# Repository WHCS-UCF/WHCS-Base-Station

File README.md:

# WHCS Base Station Design

The KiCad source files for WHCS' base station board.
The published rev 1.0 board is available on [OSHPark](https://oshpark.com/shared_projects/1ZnSgowG).

## Requirements
KiCad 2013-05-18 and some extra libraries

## Board Front

## Board Back

### Author
Grant Hernandez<br/>
*Computer Engineer*

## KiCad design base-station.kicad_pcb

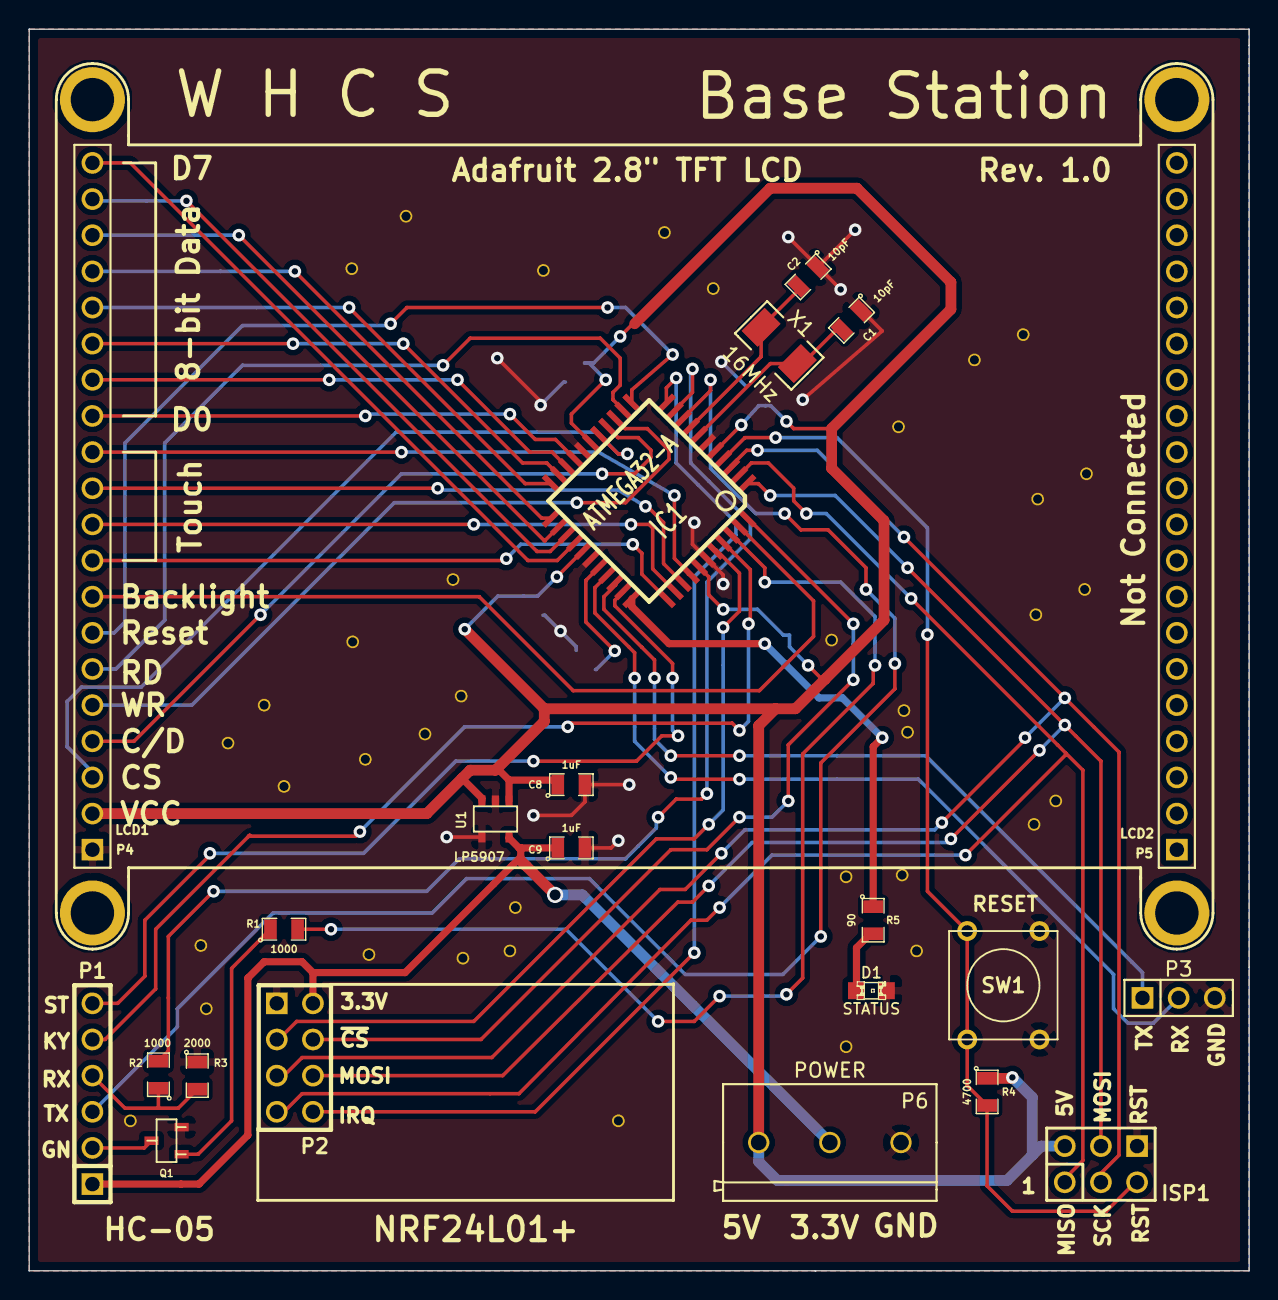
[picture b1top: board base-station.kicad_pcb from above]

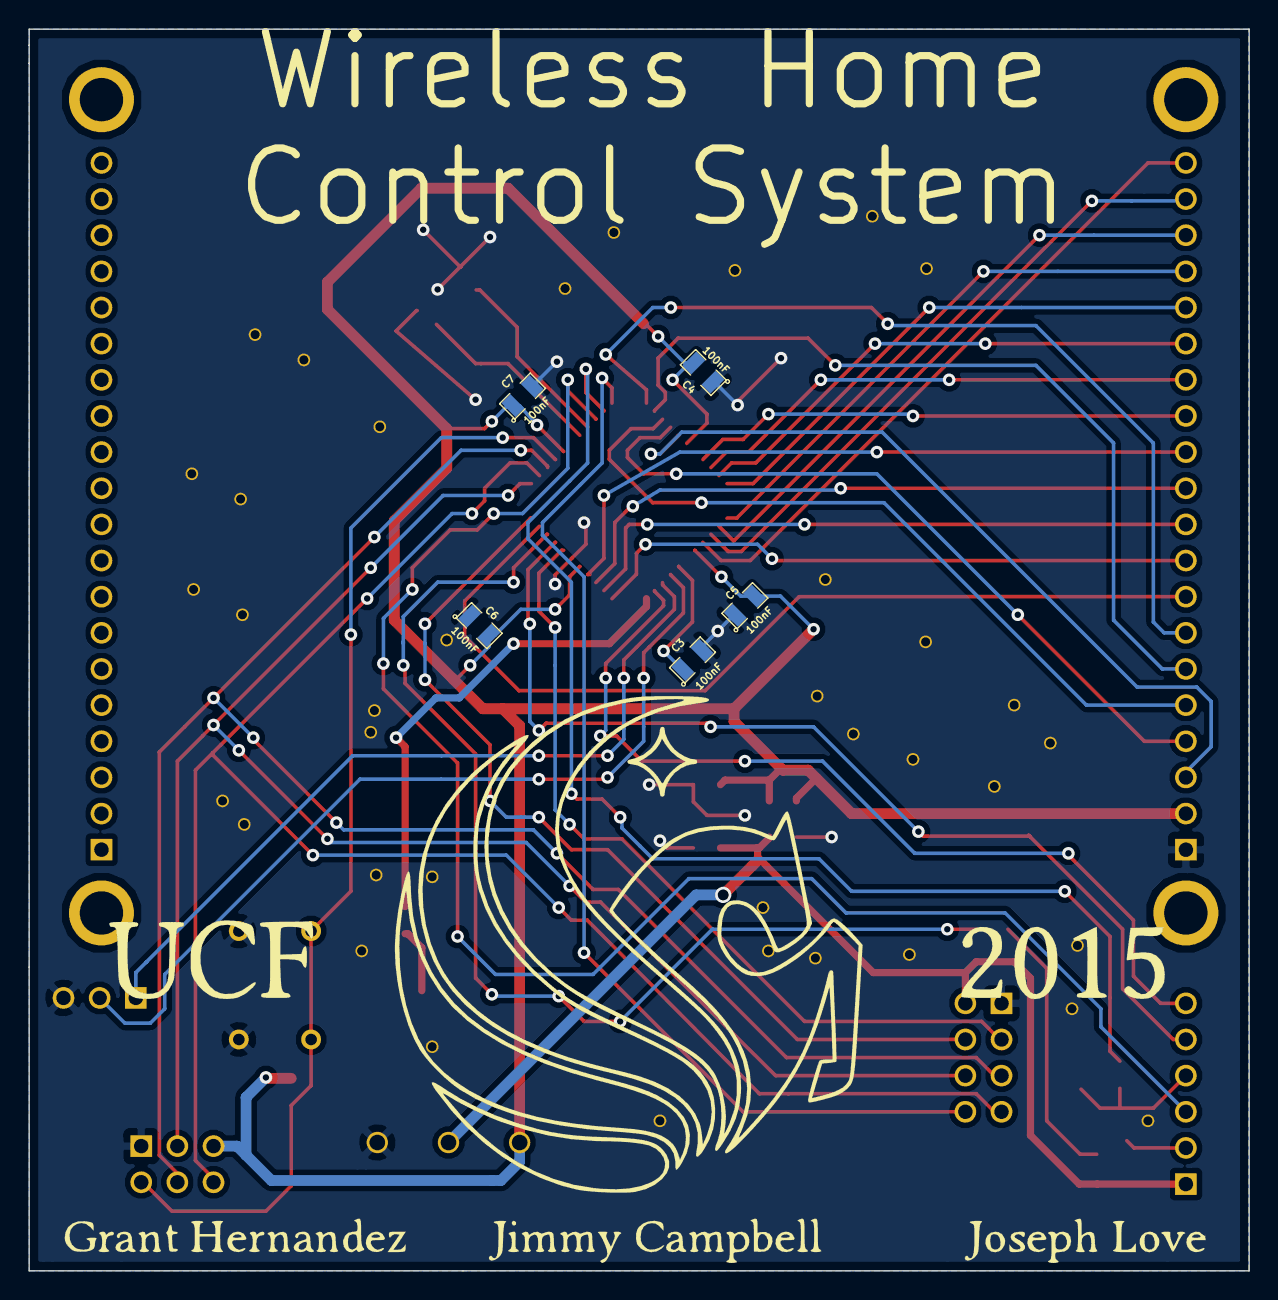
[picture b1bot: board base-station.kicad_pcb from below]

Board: 2 copper layers, 85.7 x 87.2 mm, 27 parts (5 on the bottom side), 43 nets.

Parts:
C1, C2: 10pF; SM0805
C3, C4, C5, C6, C7: 100nF; SM0805
C8, C9: 1uF; SM0805
D1: STATUS; LED-0805
IC1: ATMEGA32-A; TQFP44
ISP1: ISP; pin_array_3x2
P1: HC-05; PIN_ARRAY-6X1
P2: NRF24L01+; pin_array_4x2
P3: SERIAL; PIN_ARRAY_3X1
P4: LCD1; PIN_ARRAY_20X1
P5: LCD2; PIN_ARRAY_20X1
P6: POWER; terminal-282836-3
Q1: BTEN; sot23
R1, R2: 1000; SM0805
R3: 2000; SM0805
R4: 4700; SM0805
R5: 90; SM0805
SW1: RESET; SW_PUSH_SMALL
U1: LP5907; SOT23-5
X1: 16MHz; 2-SMD

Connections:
/3V3: C9.1, P1.1, P2.2, P6.2, U1.5
/BTEN: IC1.42, R1.2
/CD: IC1.15, P4.4
/CE: IC1.40, P2.3
/CSN: IC1.44, P2.4
/D0: IC1.19, P4.13
/D1: IC1.20, P4.14
/D2: IC1.21, P4.15
/D3: IC1.22, P4.16
/D4: IC1.23, P4.17
/D5: IC1.24, P4.18
/D6: IC1.25, P4.19
/D7: IC1.26, P4.20
/HC_GND: P1.2, Q1.2
/IRQ: IC1.11, P2.8
/KEY: IC1.41, P1.5
/LCS: IC1.16, P4.3
/LITE: IC1.43, P4.8
/LRST: IC1.12, P4.7
/MISO: IC1.2, ISP1.1, P2.7
/MOSI: IC1.1, ISP1.4, P2.6
/PA4: IC1.33, R5.1
/RD: IC1.13, P4.6
/RST: IC1.4, ISP1.5, R4.2, SW1.1
/RX: IC1.9, P1.3
/RX_SOFT: IC1.30, P3.2
/SCK: IC1.3, ISP1.3, P2.5
/STATUS: IC1.32, P1.6
/TX: IC1.10, R2.2
/TX_SOFT: IC1.31, P3.1
/VCC: C4.2, C5.2, C6.2, C7.1, C8.1, IC1.5, IC1.17, IC1.27, IC1.38, ISP1.2, P4.2, P6.1, R4.1, U1.1, U1.3
/WR: IC1.14, P4.5
/X+: IC1.34, P4.9
/X-: IC1.36, P4.11
/Y+: IC1.35, P4.10
/Y-: IC1.37, P4.12
GND: C1.1, C2.1, C3.2, C4.1, C5.1, C6.1, C7.2, C8.2, C9.2, D1.2, IC1.6, IC1.18, IC1.28, IC1.39, ISP1.6, P2.1, P3.3, P4.1, P6.3, Q1.3, R3.1, SW1.2, U1.2, U1.4
unnamed: C1.2, IC1.7, X1.2
unnamed: C2.2, IC1.8, X1.1
unnamed: Q1.1, R1.1
unnamed: P1.4, R2.1, R3.2
unnamed: D1.1, R5.2
unnamed: C3.1, IC1.29

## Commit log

2015-05-26 Initial commit for the WHCS base station
2015-05-26 Added README.md
2015-06-12 Board revision 1.0
2015-06-13 Minor power track edits
2015-06-13 Fix LCD and HC-05 wiring mixups. Improved pours
2015-06-14 More ground pour vias. Silk screen adjustments
2015-06-14 Moved HC-05 NMOS to low-side
2015-06-14 Minor silk screen adjustments for the LCD
2015-06-15 Added UCF logo
2015-06-15 Lower LCD support drill clearances to 0.02in
2015-06-15 Add Wireless Home Control System text to B.SilkS
2015-06-15 OSHPark Submit
2015-06-15 Adjust Via drill size (seen from OSHPark picture)
2015-06-15 Fix ISP SilkS bug and revision bump
2015-07-30 Add boardshots for rev 1.0
2015-07-30 Readjust README.md formatting
